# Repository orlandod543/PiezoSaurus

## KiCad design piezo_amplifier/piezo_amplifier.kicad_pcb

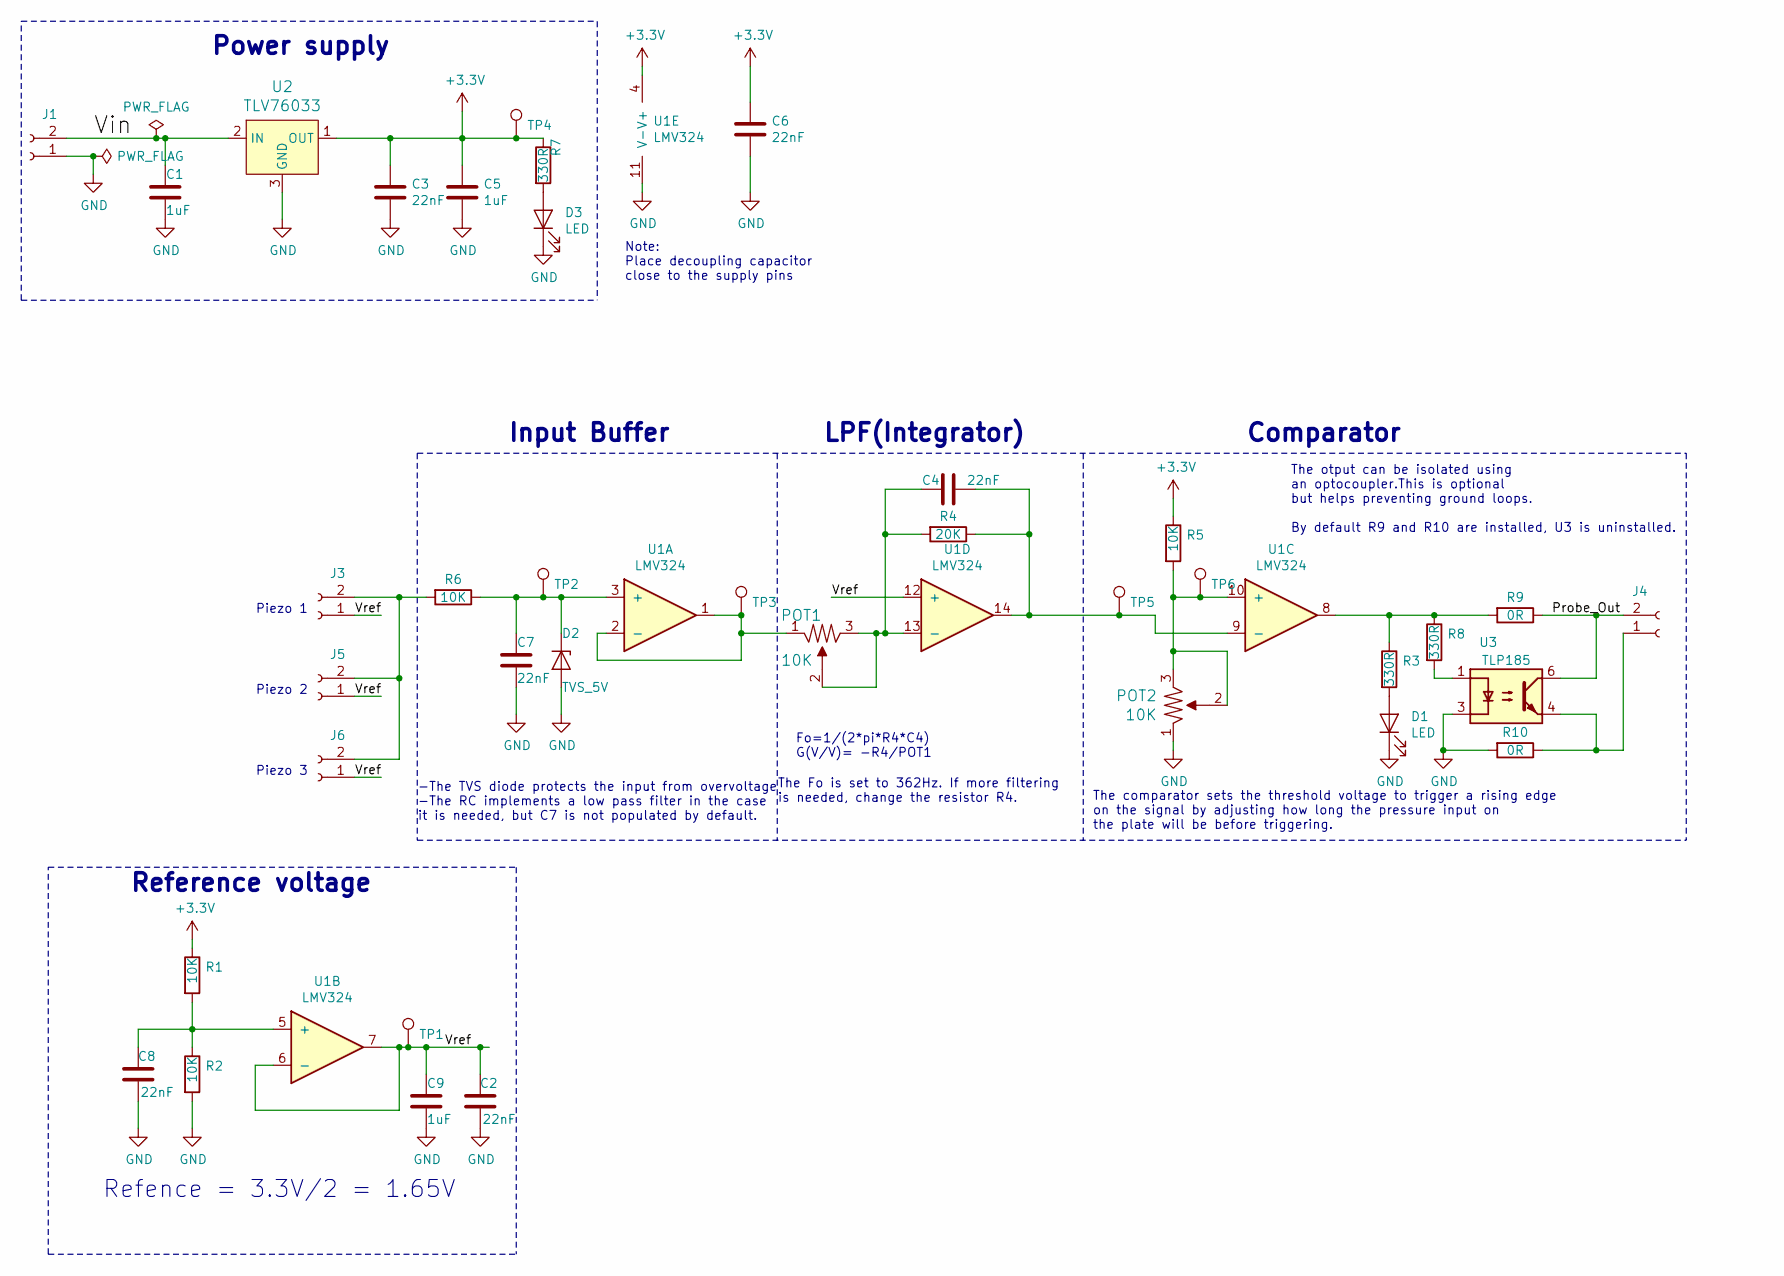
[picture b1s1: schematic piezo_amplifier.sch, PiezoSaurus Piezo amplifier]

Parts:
C1, C5, C9: 1uF; C_0603_1608Metric_Pad1.05x0.95mm_HandSolder; MPN C1608X7R1V105K080AC
C2, C3, C4, C6, C7, C8: 22nF; C_0603_1608Metric_Pad1.05x0.95mm_HandSolder; MPN CGA3E2X7R1H223K080AA
D1: LED; LED_0603_1608Metric
D2: TVS_5V; D_SOD-123; MPN SMF5.0A
D3: LED; LED_0603_1608Metric; MPN 150060VS75000
J1, J3, J4, J5, J6: S2B-XH-A-1; JST_XH_S2B-XH-A_1x02_P2.50mm_Horizontal; MPN S2B-XH-A_(LF)(SN)
POT1, POT2: 10K; Trimpot_3.8mmx3.6mm_TC33X-2-103E; MPN TC33X-2-103E; Digi-Key_PN TC33X-103ETR-ND
R1, R2, R5, R6: 10K; R_0603_1608Metric
R3, R7, R8: 330R; R_0603_1608Metric
R4: 20K; R_0603_1608Metric
R9, R10: 0R; R_0603_1608Metric
TP1, TP2, TP3, TP4, TP5, TP6: TestPoint; TestPoint_Loop_D1.80mm_Drill1.0mm_Beaded
U1: LMV324; SOIC-14_3.9x8.7mm_P1.27mm; MPN LMV324IDR
U2: TLV76033; SOT-23; MPN TLV76033DBZT; Digi-Key_PN 296-47016-1-ND
U3: TLP185; SOIC-4_4.55x3.7mm_P2.54mm; MPN TLP185(GR,E(O

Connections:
+3V3: C3.1, C5.1, C6.1, R1.1, R5.1, R7.1, TP4.1, U1.4 (V+), U2.1 (OUT)
/Probe_Out: J4.2, R9.1, U3.6
/Vin: C1.1, J1.2, U2.2 (IN)
/Vref: C2.2, C9.1, J3.1, J5.1, J6.1, TP1.1, U1.6 (-), U1.7, U1.12 (+)
GND: C1.2, C2.1, C3.2, C5.2, C6.2, C7.2, C8.1, C9.2, D1.1 (K), D2.2 (A), D3.1 (K), J1.1, POT2.1 (CCW), R2.2, R10.2, U1.11 (V-), U2.3 (GND), U3.3
unnamed: C4.1, R4.1, TP5.1, U1.9 (-), U1.14
unnamed: C4.2, POT1.2 (Wiper), POT1.3 (CW), R4.2, U1.13 (-)
unnamed: C7.1, D2.1 (K), R6.1, TP2.1, U1.3 (+)
unnamed: C8.2, R1.2, R2.1, U1.5 (+)
unnamed: D1.2 (A), R3.2
unnamed: D3.2 (A), R7.2
unnamed: J3.2, J5.2, J6.2, R6.2
unnamed: J4.1, R10.1, U3.4
unnamed: POT1.1 (CCW), TP3.1, U1.1, U1.2 (-)
unnamed: POT2.2 (Wiper), POT2.3 (CW), R5.2, TP6.1, U1.10 (+)
unnamed: R3.1, R8.1, R9.2, U1.8
unnamed: R8.2, U3.1

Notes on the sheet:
Power supply
Note: Place decoupling capacitor close to the supply pins
Refence = 3.3V/2 = 1.65V
Reference voltage
Input Buffer
-The TVS diode protects the input from overvoltage -The RC implements a low pass filter in the case it is needed, but C7 is not populated by default.
Fo=1/(2*pi*R4*C4) G(V/V)= -R4/POT1
The Fo is set to 362Hz. If more filtering is needed, change the resistor R4.
LPF(Integrator)
The comparator sets the threshold voltage to trigger a rising edge on the signal by adjusting how long the pressure input on the plate will be before triggering.
Comparator
Piezo 1
Piezo 2
Piezo 3
The otput can be isolated using an optocoupler.This is optional but helps preventing ground loops. By default R9 and R10 are installed, U3 is uninstalled.

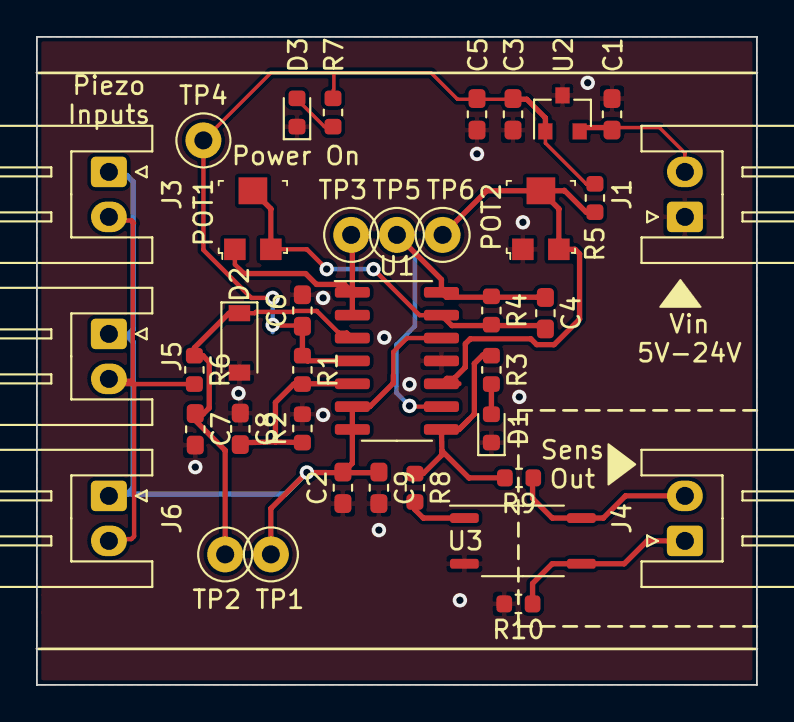
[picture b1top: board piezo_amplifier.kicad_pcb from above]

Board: 2 copper layers, 40.0 x 36.0 mm, 38 parts (0 on the bottom side), 17 nets.

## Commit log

2019-04-27 PiezoSaurus v1.0 released. Production files generated. Ready for testing:
2019-04-28 Add logo and minor silkscreen fixes
2019-04-28 Add Logo on silkscreen
2020-02-21 Simulations for V2.0 done.
2020-02-27 add .log to gitignore
2020-02-27 Schematic for V2.0 done
2020-04-11 PCB and schematics files finished, ready for release.
2020-04-12 Version V2.0 released
2020-04-12 Piezo amplifier V2.0 released. Updated with the new library convention to show not installed components and standardizing fields.
2020-04-12 fixup! Piezo amplifier V2.0 released. Updated with the new library convention to show not installed components and standardizing fields.
2020-04-13 fixup! fixup! Piezo amplifier V2.0 released. Updated with the new library convention to show not installed components and standardizing fields.
